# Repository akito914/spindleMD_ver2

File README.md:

# spindleMD_ver2

CNCフライスのスピンドル用DCモータドライバです。

主な仕様
- モータ用電源入力：DC141V
- ゲートドライブ用電源入力：DC12V
- 制御系電源入力：DC12V
- 想定モータ出力：400W
- モータ線電流フィードバック
- リンク電圧フィードバック
- マイコン：STM32F303K8T6
- インターフェース：I2C, UART
- ABZエンコーダ入力
- GPIO

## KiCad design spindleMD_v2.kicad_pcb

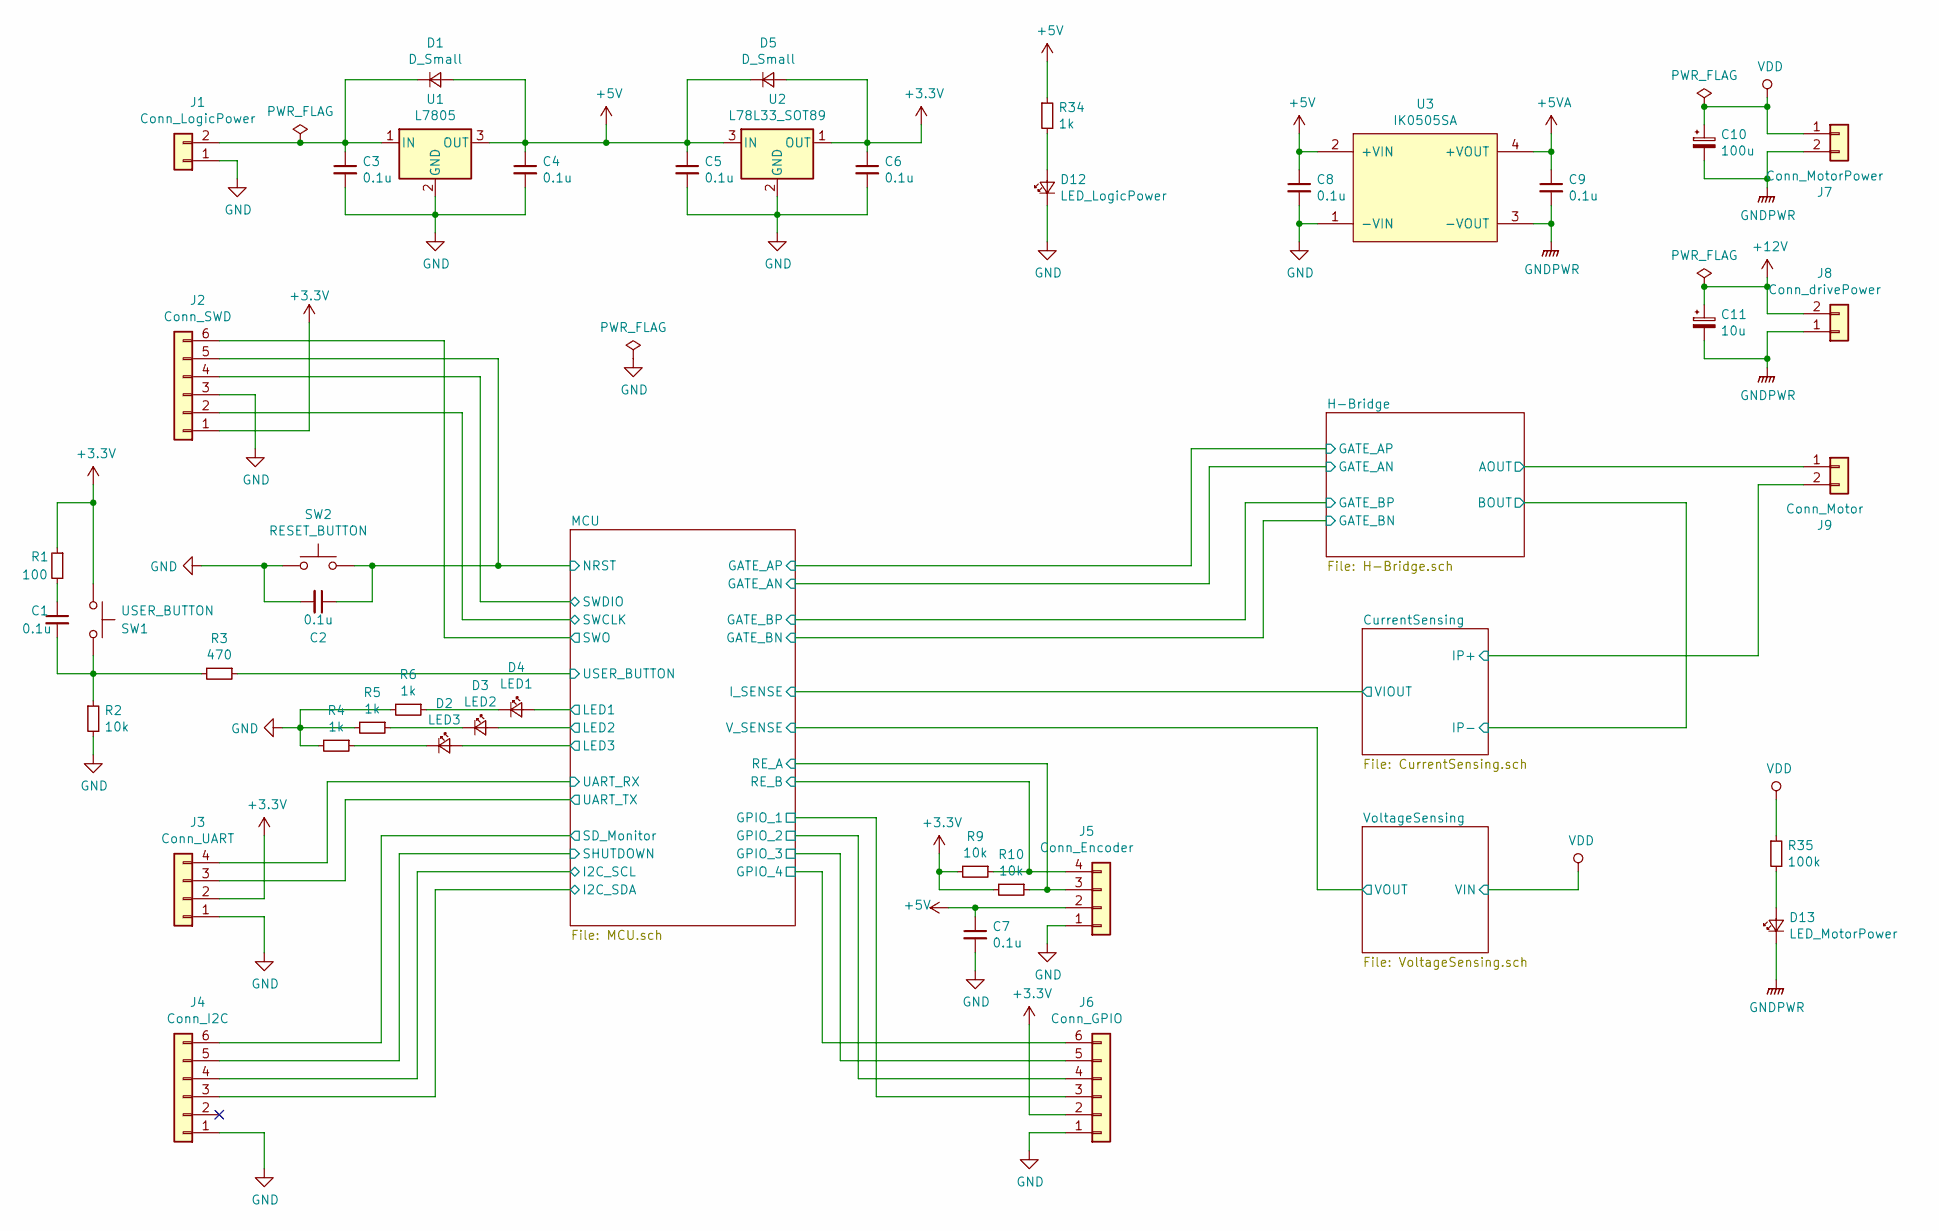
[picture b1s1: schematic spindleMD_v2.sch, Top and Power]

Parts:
C1, C2, C3, C4, C5, C6, C7, C8, C9: 0.1u; C_0603_HandSoldering
C10: 100u; CP_Radial_D10.0mm_P5.00mm
C11: 10u; C_0603_HandSoldering
D1, D5: D_Small; D_TUMD2
D2: LED3; LED_0603_HandSoldering
D3: LED2; LED_0603_HandSoldering
D4: LED1; LED_0603_HandSoldering
D12: LED_LogicPower; LED_0603_HandSoldering
D13: LED_MotorPower; LED_0603_HandSoldering
J1: Conn_LogicPower; JST_XH_B02B-XH-A_02x2.50mm_Straight
J2: Conn_SWD; JST_PH_B6B-PH-K_06x2.00mm_Straight
J3: Conn_UART; JST_XH_B04B-XH-A_04x2.50mm_Straight
J4: Conn_I2C; JST_XH_B06B-XH-A_06x2.50mm_Straight
J5: Conn_Encoder; JST_XH_B04B-XH-A_04x2.50mm_Straight
J6: Conn_GPIO; JST_XH_B06B-XH-A_06x2.50mm_Straight
J7: Conn_MotorPower; JST_VH_B2P-VH-B_2x3.96mm_Vertical
J8: Conn_drivePower; JST_XH_B02B-XH-A_02x2.50mm_Straight
J9: Conn_Motor; JST_VH_B2P-VH-B_2x3.96mm_Vertical
R1: 100; R_0603_HandSoldering
R2, R9, R10: 10k; R_0603_HandSoldering
R3: 470; R_0603_HandSoldering
R4, R5, R6, R34: 1k; R_0603_HandSoldering
R35: 100k; R_0603_HandSoldering
SW1: USER_BUTTON; LS6J2M
SW2: RESET_BUTTON; LS6J2M
U1: L7805; TO-252-2_Rectifier
U2: L78L33_SOT89; SOT-89-3_Handsoldering
U3: IK0505SA

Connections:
+3V3: C6.1, D5.2 (A), J2.1, J3.2, J6.2, R1.1, R9.2, R10.2, SW1.1, U2.1 (OUT); also elsewhere on the board
+5V: C4.1, C5.1, C7.1, C8.1, D1.2 (A), D5.1 (K), J5.2, R34.1, U1.3 (OUT), U2.3 (IN), U3.2 (+VIN); also elsewhere on the board
+5VA: C9.1, U3.4 (+VOUT); also elsewhere on the board
+12V: C11.1, J8.2; also elsewhere on the board
/CurrentSensing/IP+: J9.2; also elsewhere on the board
/H-Bridge/AOUT: J9.1; also elsewhere on the board
/MCU/GPIO_1: J6.3; also elsewhere on the board
/MCU/GPIO_2: J6.4; also elsewhere on the board
/MCU/GPIO_3: J6.5; also elsewhere on the board
/MCU/GPIO_4: J6.6; also elsewhere on the board
/MCU/I2C_SCL: J4.4; also elsewhere on the board
/MCU/I2C_SDA: J4.3; also elsewhere on the board
/MCU/LED1: D4.2 (A); also elsewhere on the board
/MCU/LED2: D3.2 (A); also elsewhere on the board
/MCU/LED3: D2.2 (A); also elsewhere on the board
/MCU/NRST: C2.1, J2.5, SW2.2; also elsewhere on the board
/MCU/RE_A: J5.3, R10.1; also elsewhere on the board
/MCU/RE_B: J5.4, R9.1; also elsewhere on the board
/MCU/SD_Monitor: J4.6; also elsewhere on the board
/MCU/SHUTDOWN: J4.5; also elsewhere on the board
/MCU/SWCLK: J2.2; also elsewhere on the board
/MCU/SWDIO: J2.4; also elsewhere on the board
/MCU/SWO: J2.6; also elsewhere on the board
/MCU/UART_RX: J3.4; also elsewhere on the board
/MCU/UART_TX: J3.3; also elsewhere on the board
/MCU/USER_BUTTON: R3.1; also elsewhere on the board
GND: C2.2, C3.2, C4.2, C5.2, C6.2, C7.2, C8.2, D12.1 (K), J1.1, J2.3, J3.1, J4.1, J5.1, J6.1, R2.2, R4.2, R5.2, R6.2, SW2.1, U1.2 (GND), U2.2 (GND), U3.1 (-VIN); also elsewhere on the board
GNDPWR: C9.2, C10.2, C11.2, D13.1 (K), J7.2, J8.1, U3.3 (-VOUT); also elsewhere on the board
unnamed: C1.1, R1.2
unnamed: C1.2, R2.1, R3.2, SW1.2
unnamed: C3.1, D1.1 (K), J1.2, U1.1 (IN)
unnamed: D2.1 (K), R4.1
unnamed: D3.1 (K), R5.1
unnamed: D4.1 (K), R6.1
unnamed: D12.2 (A), R34.2
unnamed: D13.2 (A), R35.2
VDD: C10.1, J7.1, R35.1; also elsewhere on the board

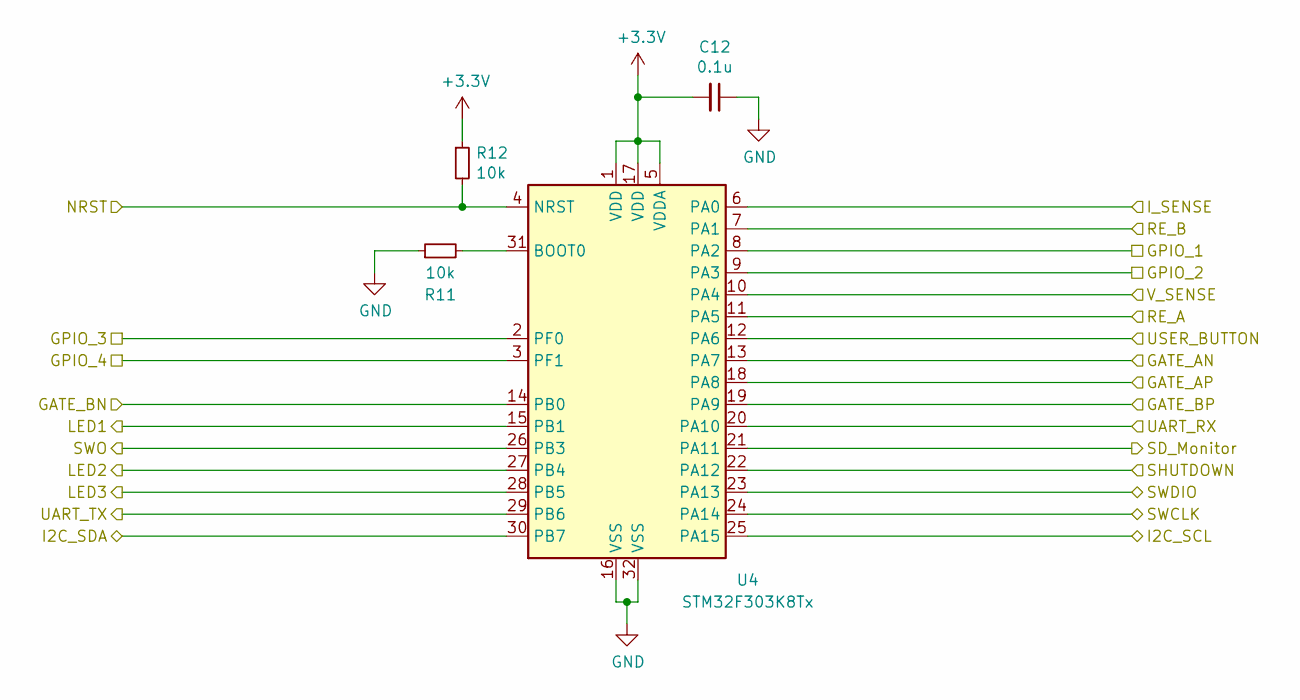
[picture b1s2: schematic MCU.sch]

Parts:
C12: 0.1u; C_0603_HandSoldering
R11, R12: 10k; R_0603_HandSoldering
U4: STM32F303K8Tx; LQFP-32_7x7mm_Pitch0.8mm

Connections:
+3V3: C12.2, R12.1, U4.1 (VDD), U4.5 (VDDA), U4.17 (VDD); also elsewhere on the board
/H-Bridge/GATE_AN: U4.13 (PA7); also elsewhere on the board
/H-Bridge/GATE_AP: U4.18 (PA8); also elsewhere on the board
/H-Bridge/GATE_BN: U4.14 (PB0); also elsewhere on the board
/H-Bridge/GATE_BP: U4.19 (PA9); also elsewhere on the board
/MCU/GPIO_1: U4.8 (PA2); also elsewhere on the board
/MCU/GPIO_2: U4.9 (PA3); also elsewhere on the board
/MCU/GPIO_3: U4.2 (PF0); also elsewhere on the board
/MCU/GPIO_4: U4.3 (PF1); also elsewhere on the board
/MCU/I2C_SCL: U4.25 (PA15); also elsewhere on the board
/MCU/I2C_SDA: U4.30 (PB7); also elsewhere on the board
/MCU/I_SENSE: U4.6 (PA0); also elsewhere on the board
/MCU/LED1: U4.15 (PB1); also elsewhere on the board
/MCU/LED2: U4.27 (PB4); also elsewhere on the board
/MCU/LED3: U4.28 (PB5); also elsewhere on the board
/MCU/NRST: R12.2, U4.4 (NRST); also elsewhere on the board
/MCU/RE_A: U4.11 (PA5); also elsewhere on the board
/MCU/RE_B: U4.7 (PA1); also elsewhere on the board
/MCU/SD_Monitor: U4.21 (PA11); also elsewhere on the board
/MCU/SHUTDOWN: U4.22 (PA12); also elsewhere on the board
/MCU/SWCLK: U4.24 (PA14); also elsewhere on the board
/MCU/SWDIO: U4.23 (PA13); also elsewhere on the board
/MCU/SWO: U4.26 (PB3); also elsewhere on the board
/MCU/UART_RX: U4.20 (PA10); also elsewhere on the board
/MCU/UART_TX: U4.29 (PB6); also elsewhere on the board
/MCU/USER_BUTTON: U4.12 (PA6); also elsewhere on the board
/VoltageSensing/VOUT: U4.10 (PA4); also elsewhere on the board
GND: C12.1, R11.1, U4.16 (VSS), U4.32 (VSS); also elsewhere on the board
unnamed: R11.2, U4.31 (BOOT0)

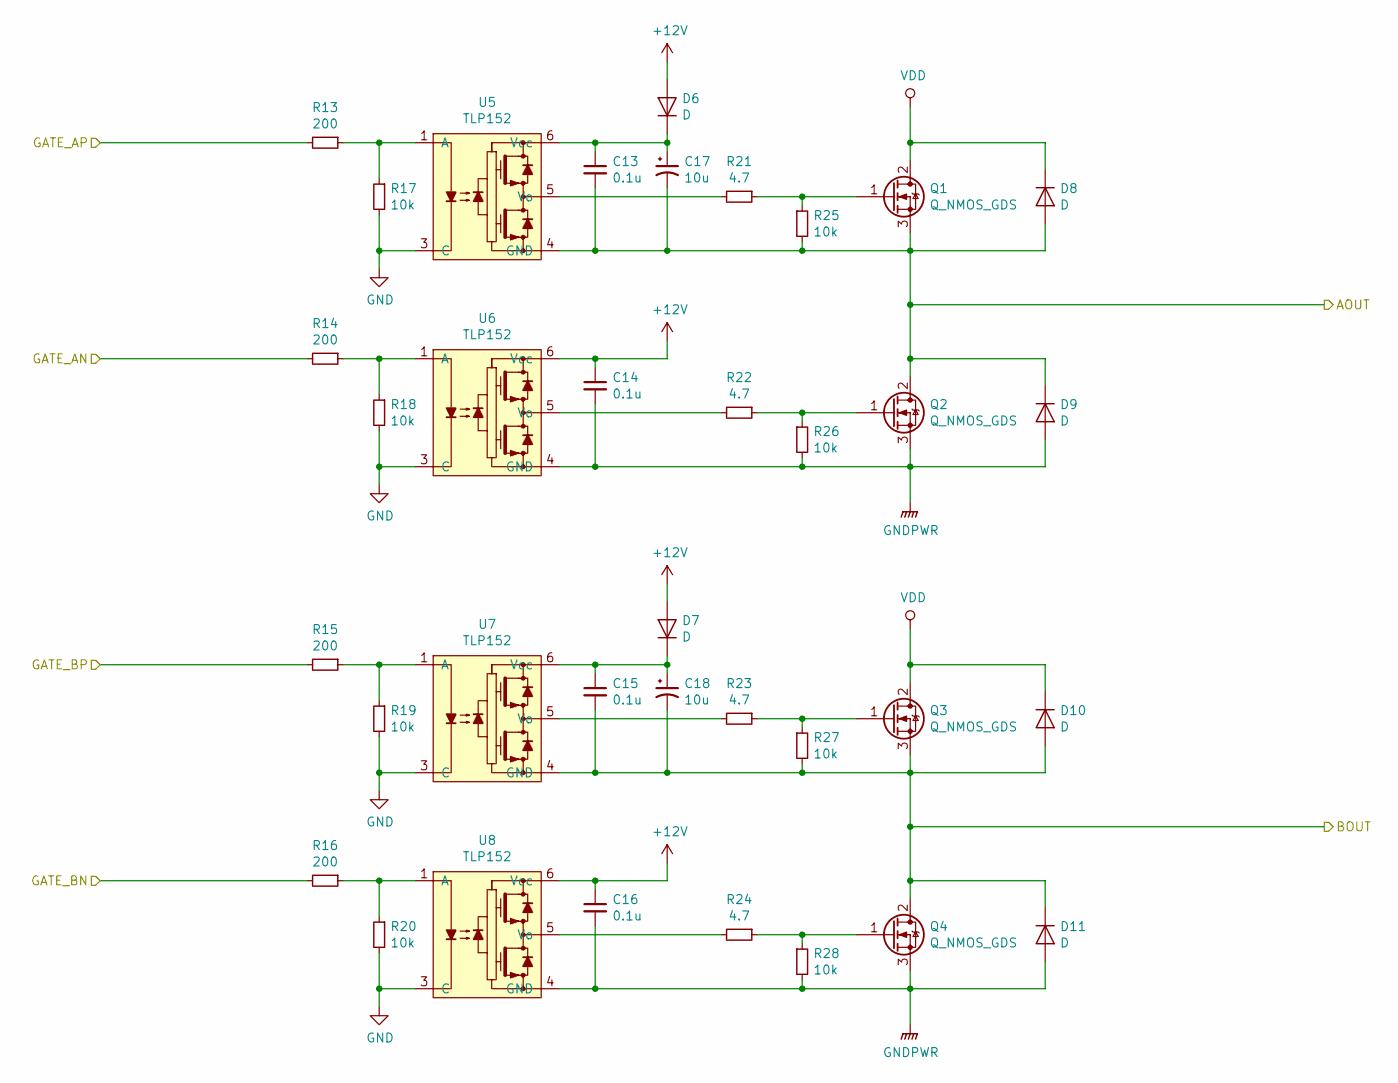
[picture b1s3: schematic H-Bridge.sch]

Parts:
C13, C14, C15, C16: 0.1u; C_0603_HandSoldering
C17, C18: 10u; C_0603_HandSoldering
D6, D7: D; D_TUMD2
D8, D9, D10, D11: D; D_SMB
Q1, Q2, Q3, Q4: Q_NMOS_GDS; TO-220-3_Horizontal_Reversed
R13, R14, R15, R16: 200; R_0603_HandSoldering
R17, R18, R19, R20, R25, R26, R27, R28: 10k; R_0603_HandSoldering
R21, R22, R23, R24: 4.7; R_0805_HandSoldering
U5, U6, U7, U8: TLP152; SO-5_4.4x3.6mm_Pitch1.27mm

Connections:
+12V: C14.1, C16.1, D6.2 (A), D7.2 (A), U6.6 (Vcc), U8.6 (Vcc); also elsewhere on the board
/H-Bridge/AOUT: C13.2, C17.2, D8.2 (A), D9.1 (K), Q1.3 (S), Q2.2 (D), R25.2, U5.4 (GND); also elsewhere on the board
/H-Bridge/BOUT: C15.2, C18.2, D10.2 (A), D11.1 (K), Q3.3 (S), Q4.2 (D), R27.2, U7.4 (GND); also elsewhere on the board
/H-Bridge/GATE_AN: R14.2; also elsewhere on the board
/H-Bridge/GATE_AP: R13.2; also elsewhere on the board
/H-Bridge/GATE_BN: R16.2; also elsewhere on the board
/H-Bridge/GATE_BP: R15.2; also elsewhere on the board
GND: R17.2, R18.2, R19.2, R20.2, U5.3 (C), U6.3 (C), U7.3 (C), U8.3 (C); also elsewhere on the board
GNDPWR: C14.2, C16.2, D9.2 (A), D11.2 (A), Q2.3 (S), Q4.3 (S), R26.2, R28.2, U6.4 (GND), U8.4 (GND); also elsewhere on the board
unnamed: C13.1, C17.1, D6.1 (K), U5.6 (Vcc)
unnamed: C15.1, C18.1, D7.1 (K), U7.6 (Vcc)
unnamed: Q1.1 (G), R21.1, R25.1
unnamed: Q2.1 (G), R22.1, R26.1
unnamed: Q3.1 (G), R23.1, R27.1
unnamed: Q4.1 (G), R24.1, R28.1
unnamed: R13.1, R17.1, U5.1 (A)
unnamed: R14.1, R18.1, U6.1 (A)
unnamed: R15.1, R19.1, U7.1 (A)
unnamed: R16.1, R20.1, U8.1 (A)
unnamed: R21.2, U5.5 (Vo)
unnamed: R22.2, U6.5 (Vo)
unnamed: R23.2, U7.5 (Vo)
unnamed: R24.2, U8.5 (Vo)
VDD: D8.1 (K), D10.1 (K), Q1.2 (D), Q3.2 (D); also elsewhere on the board

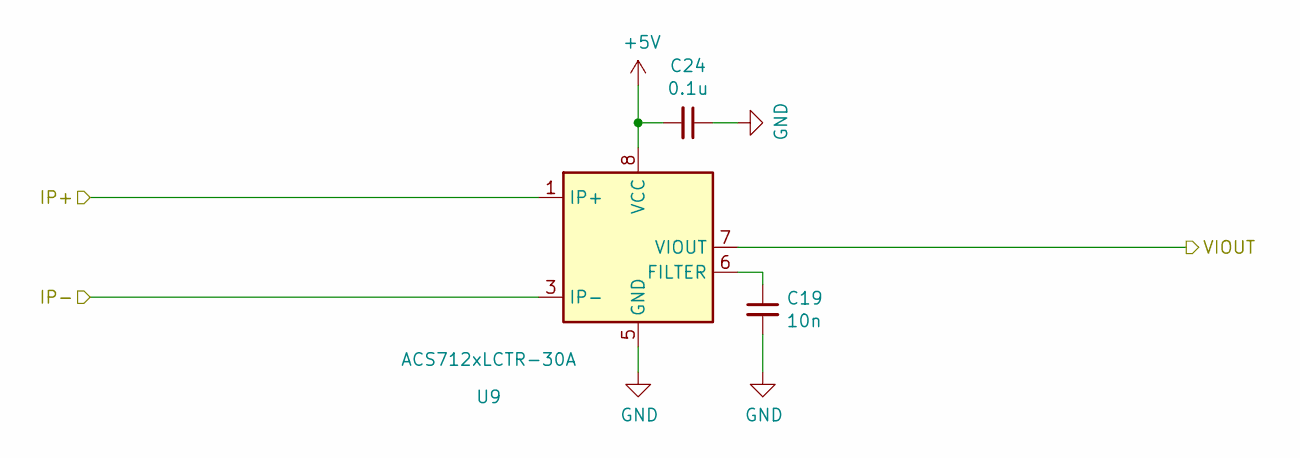
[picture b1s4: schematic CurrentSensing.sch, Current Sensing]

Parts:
C19: 10n; C_0603_HandSoldering
C24: 0.1u; C_0603_HandSoldering
U9: ACS712xLCTR-30A; SOIC-8_3.9x4.9mm_Pitch1.27mm

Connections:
+5V: C24.2, U9.8 (VCC); also elsewhere on the board
/CurrentSensing/IP+: U9.1 (IP+), U9.2 (IP+); also elsewhere on the board
/H-Bridge/BOUT: U9.3 (IP-), U9.4 (IP-); also elsewhere on the board
/MCU/I_SENSE: U9.7 (VIOUT); also elsewhere on the board
GND: C19.2, C24.1, U9.5 (GND); also elsewhere on the board
unnamed: C19.1, U9.6 (FILTER)

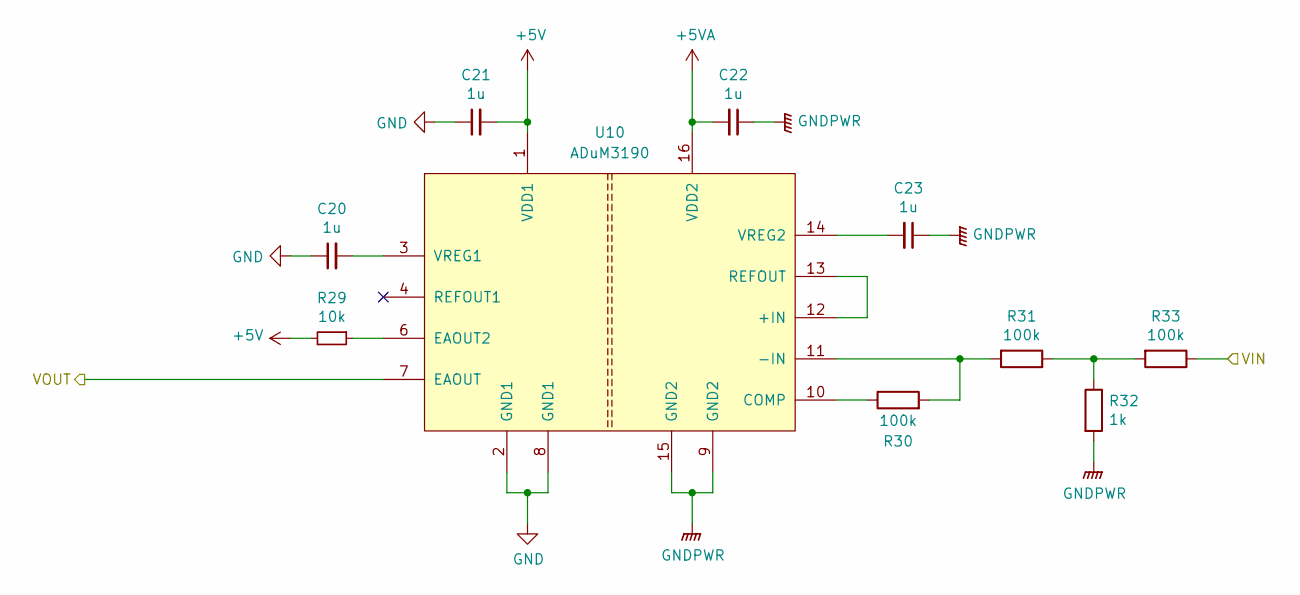
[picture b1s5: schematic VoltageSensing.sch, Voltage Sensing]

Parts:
C20, C21, C22, C23: 1u; C_0603_HandSoldering
R29: 10k; R_0603_HandSoldering
R30, R31, R33: 100k; R_0603_HandSoldering
R32: 1k; R_0603_HandSoldering
U10: ADuM3190; QSOP-16_3.9x4.9mm_Pitch0.635mm

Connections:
+5V: C21.2, R29.2, U10.1 (VDD1); also elsewhere on the board
+5VA: C22.2, U10.16 (VDD2); also elsewhere on the board
/VoltageSensing/VOUT: U10.7 (EAOUT); also elsewhere on the board
GND: C20.1, C21.1, U10.2 (GND1), U10.8 (GND1); also elsewhere on the board
GNDPWR: C22.1, C23.1, R32.2, U10.9 (GND2), U10.15 (GND2); also elsewhere on the board
unnamed: C20.2, U10.3 (VREG1)
unnamed: C23.2, U10.14 (VREG2)
unnamed: R29.1, U10.6 (EAOUT2)
unnamed: R30.1, U10.10 (COMP)
unnamed: R30.2, R31.2, U10.11 (-IN)
unnamed: R31.1, R32.1, R33.2
unnamed: U10.12 (+IN), U10.13 (REFOUT)
VDD: R33.1; also elsewhere on the board

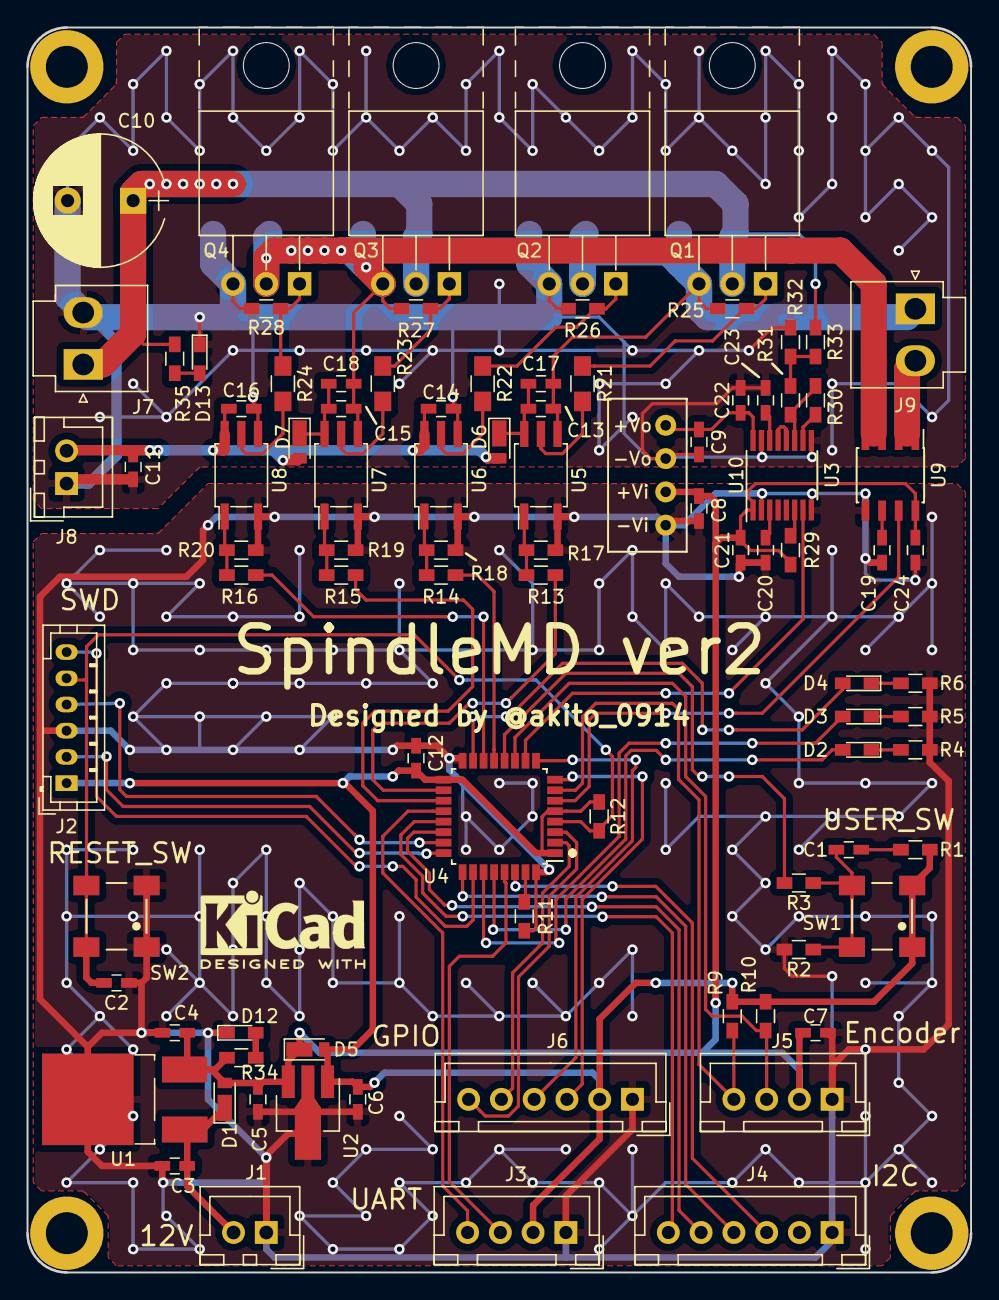
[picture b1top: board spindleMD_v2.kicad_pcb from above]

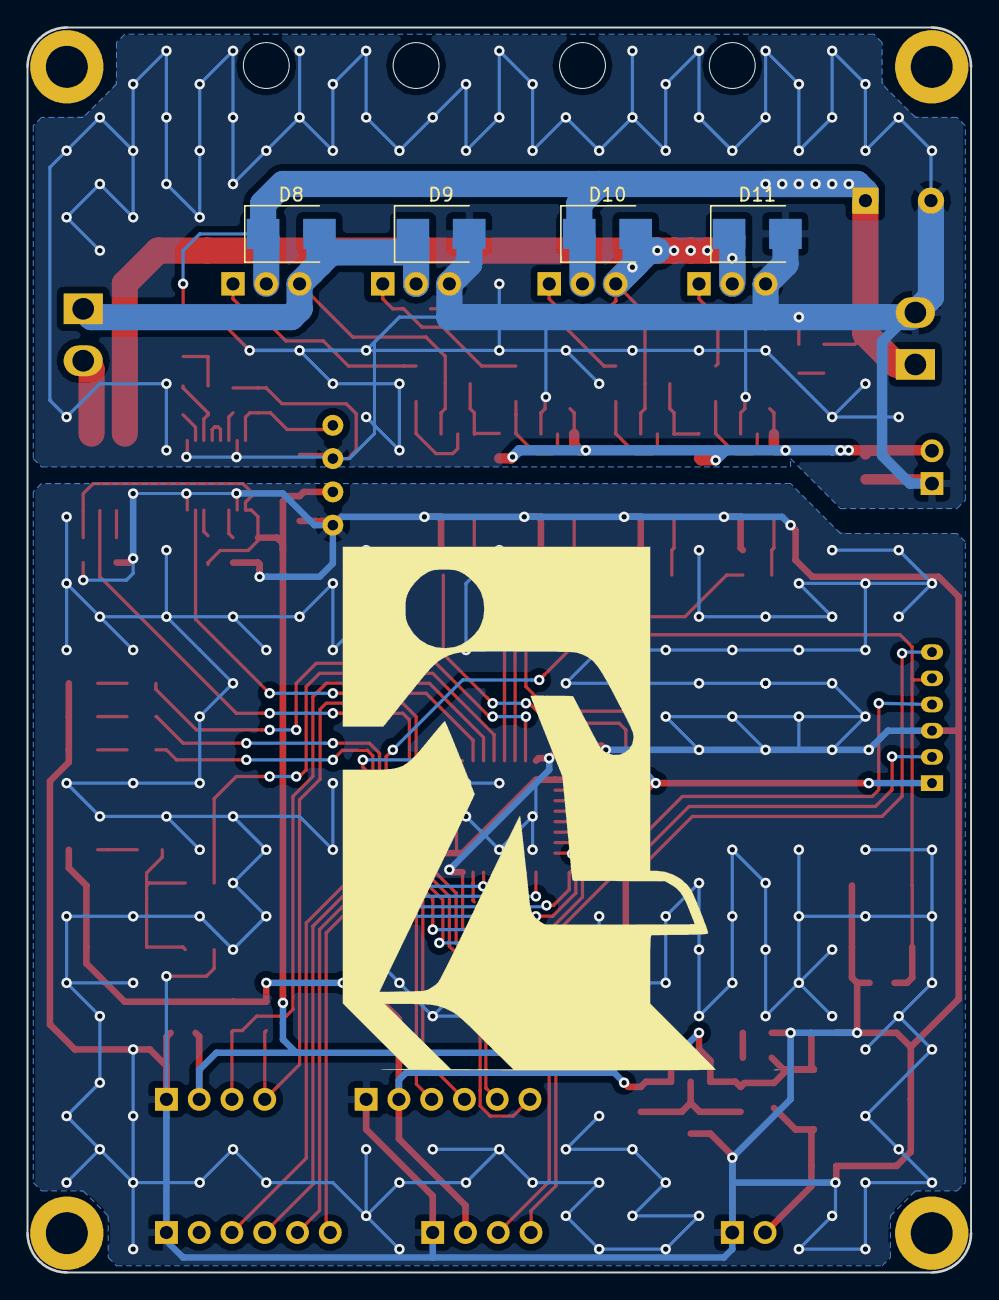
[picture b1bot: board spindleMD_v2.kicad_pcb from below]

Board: 2 copper layers, 72.0 x 95.0 mm, 95 parts (4 on the bottom side), 67 nets.

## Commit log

2019-03-03 firstcommit
    ・Hブリッジとセンシング回路を作成
    ・単相ならマイコン側でデッドタイム挿入が可能であることがわかった。
2019-03-03 デッドタイム挿入回路を削除、マイコンブロック作成
2019-03-04 第１版回路図完成
2019-03-04 powerFlag追加
2019-03-04 回路図PDF書き出し
2019-03-04 フットプリント割り付け＆Netリスト出力
2019-03-04 STM32のふっとプリント割り付け修正
2019-03-04 電源LED追加
2019-03-05 フライホイールダイオード交換
2019-03-05 パワー電源コネクタピン配置修正
2019-03-07 電流センサ電源パスコン追加
2019-03-08 アートワーク完成
2019-03-08 固定穴シルク非表示
2019-03-08 ガーバー書き出し
2019-03-08 シルク追加
2019-05-31 readmeを更新
2019-07-14 kicadバージョン更新
